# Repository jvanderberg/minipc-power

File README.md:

# minipc-power

Small power board for MCU-based emulator builds (Pico / ESP32 class with a 12 V 5" LCD). Runs from USB-C or a 1S2P
18650 pack, charges the pack whenever USB-C is plugged in, and supplies 12 V, 5 V and 3.3 V.

## Features

- **USB-C PD input:** requests 9 V (CH224Q), falls back to 5 V on non-PD chargers; TVS on VBUS.
- **Charger:** BQ25606 standalone switching charger, 1.44 A charge to 4.2 V, 1.9 A input limit. Power path: the
  board runs from USB even with a dead or missing pack. NTC input for charge-temperature limits.
- **Battery protection** for bare cells: HY2113 protector (over-charge 4.28 V, over-discharge 2.80 V, over-current,
  short circuit), 10 A fuse, reverse-polarity FET.
- **Outputs**, all switched together by one on/off switch (off by default):
  - **12 V, 0.5 A:** TPS61178 synchronous boost with output disconnect (for the LCD)
  - **5 V, 2.5 A:** TPS61088-Q1 synchronous boost with a soft-start load switch
  - **3.3 V, 1.5 A:** TPS63802 buck-boost (regulated across the whole battery range)
- **Power budget:** 15 W combined as a peak; about 10-12 W continuous in a closed box (see `docs/thermal.md`).
- **Solder pads** for everything: battery, outputs, on/off switch, NTC, status (charging, power good, 3.3 V good,
  battery voltage sense).
- **Board:** 52 x 36 mm, 4 layers (JLCPCB JLC04161H-7628), parts from LCSC; every part has its datasheet link.

## Status

Design reviewed, not yet built. Bench checks to run first: `docs/power-design.md` s9 and `docs/review-2026-10-24.md`.
`hardware/production/` predates the latest board changes: regenerate it before ordering.

## Files

- `hardware/` - KiCad 10 project (schematic, board, symbols, footprints, 3D models)
- `tools/` - the schematic and board are generated by these scripts; edit them, not the KiCad files:
  `python3 tools/gen_schematic.py && bash tools/build_board.sh` (needs KiCad 10 and
  [kicad-skills](https://github.com/jvanderberg/kicad-skills))
- `docs/requirements.md` - requirements and architecture (start here)
- `docs/power-design.md` - every component value and where it comes from
- `docs/thermal.md` - heat budget
- `docs/review-2026-10-24.md` - design review: fixed, open, owner decisions, bench checks
- `docs/layout-compliance.md` - each converter's layout against its datasheet
- `docs/skill-gaps.md` - problems found in the kicad-skills plugin while designing this board

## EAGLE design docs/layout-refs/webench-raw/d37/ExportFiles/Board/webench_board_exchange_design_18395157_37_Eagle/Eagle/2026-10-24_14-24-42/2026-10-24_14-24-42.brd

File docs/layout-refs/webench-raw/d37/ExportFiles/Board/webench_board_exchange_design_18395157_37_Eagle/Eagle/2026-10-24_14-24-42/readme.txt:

Note! You will only be recieving either a Schematic file or a 
Board file but not both at the same time.

To import your new BOARD into Eagle:
1. Start the Eagle program.
2. From the menu select "File" and then select "Open".
3. Select "Board"
4. Select the file named in the path above ending with ".BRD"
   and "Open" the file.
5. Your board should be viewable within Eagle now.

To import your new SCHEMATIC into Eagle:
1. Start the Eagle program.
2. From the menu select "File" and then select "Open".
3. Select "Schematic"
3. Select the file named in the path above ending with ".Sch"
   and "Open" the file.
4. Your board should be viewable within Eagle.

For additional information, please visit this site:
http://www.accelerated-designs.com/help/Eagle_import_BRD_SCH.html

To see a video tutorial, please visit:
http://youtu.be/F0g8oiZ5-uo

To import your new LIBRARY into Eagle:
1. Start Eagle.
2. Select File -> New -> Library from the menu.
3. In the blank library window, select File -> Script from the menu.
4. Select the EDIF tab.
5. Browse to the correct Eagle Script file (".scr" file extension) in the file "Open" window.
The exported script file will be below the path configured in Ultra Librarian under
Options -> Configuration -> "Setup" Tab -> "CAD Exports".
6. After opening the file, the script will populate the new library.
7. Use File -> Save (or Save As..) to save the library to the desired location in Eagle native format.

For additional information, please visit this site:
http://www.accelerated-designs.com/help/Eagle_import.html

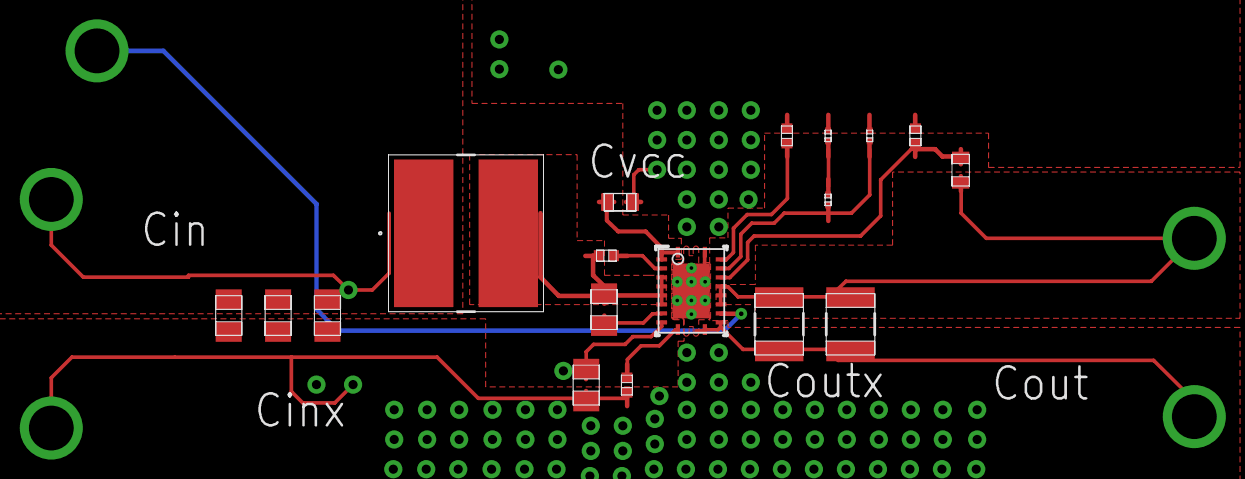
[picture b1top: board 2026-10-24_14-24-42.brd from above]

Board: 4 copper layers, 24 parts (0 on the bottom side), 13 nets.

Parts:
Cbst: 0805
Ccomp, Ccomp2: 0201
Cin2: 0805
Cin_1, Cin_2, Cin_3: 0805
Cout_1, Cout_2: 1210_280
Css: 0402
Cvcc_1, Cvcc_2: 0603
GND, GND1: TP-1502
L1: VLP8040
MODE: TP-1502
Rcomp: 0201
Rfbb: 0402
Rfbt: 0603
Rlim: 0402
Rt: 0402
U1: RHL0020A
VIN: TP-1502
VOUT: TP-1502

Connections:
0: Ccomp.2, Ccomp2.2, Cin2.2, Cin_1.2, Cin_2.2, Cin_3.2, Cout_1.2, Cout_2.2, Css.2, Cvcc_1.2, Cvcc_2.2, GND.1, GND1.1, Rfbb.2, Rlim.2, U1.11, U1.12, U1.20, U1.21
2: Cin2.1, Cin_1.1, Cin_2.1, Cin_3.1, L1.1, U1.9, VIN.1
3: Ccomp.1, Rcomp.2
4: Cvcc_1.1, Cvcc_2.1, U1.1, U1.2
5: Ccomp2.1, Rcomp.1, U1.18
9: Cout_1.1, Cout_2.1, Rfbt.1, U1.14, U1.15, U1.16, VOUT.1
11: Rfbb.1, Rfbt.2, U1.17
12: Cbst.1, L1.2, Rt.1, U1.4, U1.5, U1.6, U1.7
14: Rlim.1, U1.19
15: Rt.2, U1.3
17: MODE.1, U1.13
19: Css.1, U1.10
21: Cbst.2, U1.8

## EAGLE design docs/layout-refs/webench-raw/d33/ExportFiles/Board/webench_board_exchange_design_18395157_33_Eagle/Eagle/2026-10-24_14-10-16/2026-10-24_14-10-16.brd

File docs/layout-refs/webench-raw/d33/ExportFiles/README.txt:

## WEBENCH Design 33
Created at Sat Oct 24 14:10:02 CDT 2026
**********************************************************
***************** Schematic Instructions  ****************
**********************************************************

To import your new Schematic file into Eagle:

1. Unzip the downloaded folder files to local directory and Start Eagle.
2. Select "File"->"Open"->"Schematic..." from the menu at the top of
the screen.
3. Browse to your newly exported file and select the ".sch" file extension.
4. You should now see your schamtic available in Eagle.

**********************************************************
*******************  PCB Instructions  *******************
**********************************************************

To import your new BOARD file into Eagle:

1. Unzip the downloaded folder files to local directory and Start Eagle.
2. Select "File"->"Open"->"Board..." from the menu at the top of
the screen.
3. Browse to your newly exported file and select the ".brd" file extension.
4. Planes will need to be repoured to update the polygon fills
	1. Once your board is loaded, type "ratsnest" into the command
	   line and press the Enter key.
	2. The polygons should all be filled now.
5. You should now have an image of your board available in Eagle.

**********************************************************
*******************  LIB Instructions  *******************
**********************************************************

To import your new library into Eagle:

1. Start Eagle.
2. Select "File"->"New"->"Library" from the menu.
3. In the blank library window, select "File" -> "Execute Script"
from the menu.
5. Browse to your newly exported Eagle Script file (".scr" file extension)
6. After opening the file, the script will populate the new library.
Layer 93 should NOT exist.
7. Use "File"->Save As: "AcceleratedDesigns_Lib.lbr" and to the desired
location in Eagle native format.
8. Update schematic with the imported library, Select Library and click on Update; open the library file
	and sync. each part.

For additional information, please visit this site:
http://www.accelerated-designs.com/help/Eagle_import.html

You may also find this video helpful:
http://youtu.be/5jGuWY-Yy3Q

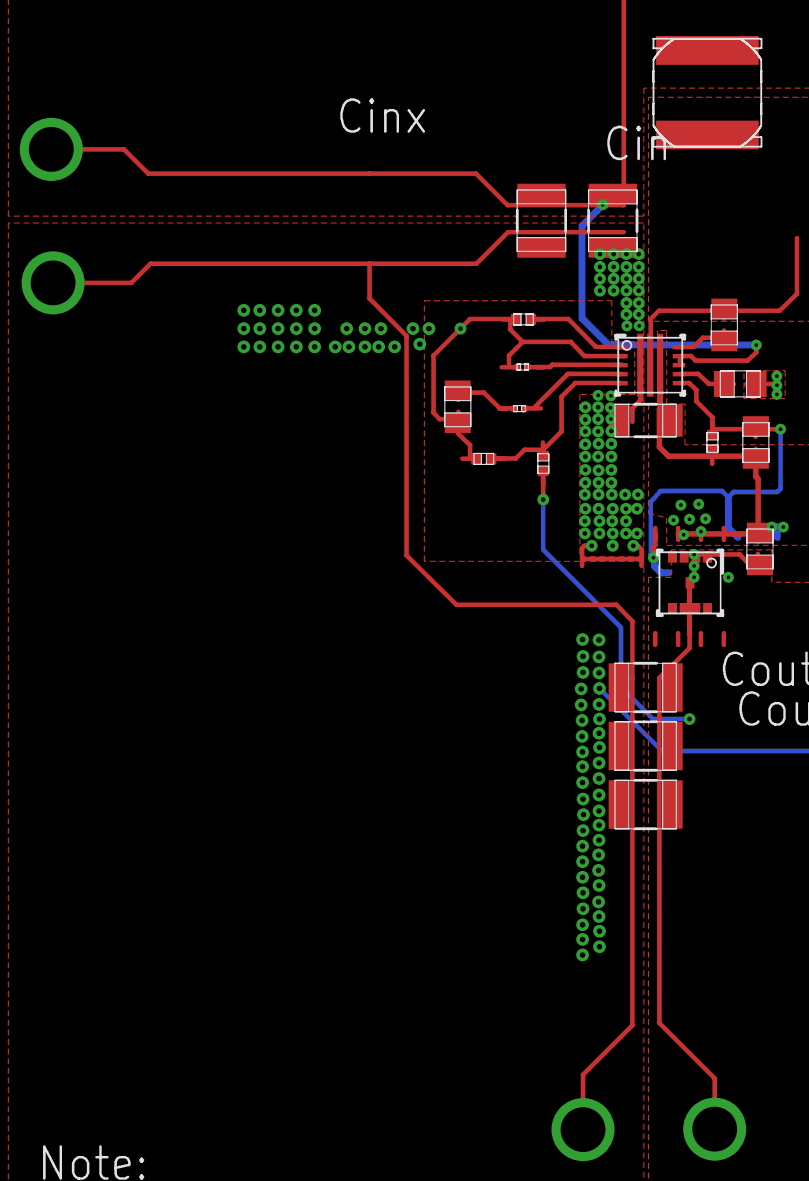
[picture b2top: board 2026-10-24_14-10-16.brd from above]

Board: 4 copper layers, 24 parts (0 on the bottom side), 13 nets.

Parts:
Cboot: 0805
Ccomp: 0805
Cgate: 0805
Cin_1, Cin_2: 1210
Cout1: 1206
Cout_1, Cout_2, Cout_3: 1210
Cvcc: 0805
GND, GND1: TP-1502
L1: DG6045C
M3: DQG0008A
Rcomp: 0201
Rfbb: 0402
Rfbt: 0402
Rgate: 0402
Rilim: 0201
Rpfet: 0805
Rt: 0402
U1: RNW0013A
VIN: TP-1502
VOUT: TP-1502

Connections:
0: Cboot.2, U1.13
1: Cgate.2, Rgate.2, U1.9
2: Cgate.1, Cout1.1, Rgate.1, Rpfet.1, U1.8
5: Rt.1, U1.1
8: Cin_1.1, Cin_2.1, L1.2, U1.11, U1.12, VIN.1
10: Cboot.1, L1.1, U1.7
11: Rfbb.1, Rfbt.2, U1.5
13: Cout_1.1, Cout_2.1, Cout_3.1, M3.1, M3.2, M3.3, M3.4, M3.5, M3.6, M3.7, M3.8, M3.9, Rfbt.1, Rpfet.2, VOUT.1
14: Ccomp.1, Rcomp.2
18: Ccomp.2, Cin_1.2, Cin_2.2, Cout1.2, Cout_1.2, Cout_2.2, Cout_3.2, Cvcc.2, GND.1, GND1.1, Rfbb.2, Rilim.2, Rt.2, U1.2, U1.6
19: Cvcc.1, U1.10
24: Rcomp.1, U1.4
27: Rilim.1, U1.3
